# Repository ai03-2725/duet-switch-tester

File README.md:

# Duet Switch Tester

A switch tester intended for use at events and storefronts.  
Displays two of each switch - one with a keycap for testing the keyfeel, and another without a keycap to show off the visuals.  
Can be assembled with a functioning PCB to pair the tester to a kiosk device for additional information display purposes.  

## Features
- FR4 sandwich case
- Designed to look visually balanced with the left column of each cluster having keycaps installed
- Fully hotswap PCB powered by a RP2040
- Roughly 1800-size to balance display quantity with practicality and shipping/transport constraints

## BOM
Necessary for all builds:
- 1x Plate
- 1x Bottom panel
- 8x M2x8 Spacers
- 16x M2x5 wafer-head screws
- 10x 8mm diameter rubber feet
  
Necessary if planning to pair the device to a webapp or similar:
- 1x PCB (Optional if you're not looking to pair the tester to a device)
- Optional hotswap standoffs for anchoring the PCB to the plate
    - 10x M2x3.5 Spacers
    - 20x M2x3 wafer-head screws

## Restrictions
As per the [license](https://github.com/ai03-2725/duet-switch-tester/blob/main/LICENSE), any modified version must be fully disclosed and open-sourced under the same license.  
  
There is no warranty, liability, or support for this project.  
If you intend to use this project, do so at your own risk and under your own responsibility.

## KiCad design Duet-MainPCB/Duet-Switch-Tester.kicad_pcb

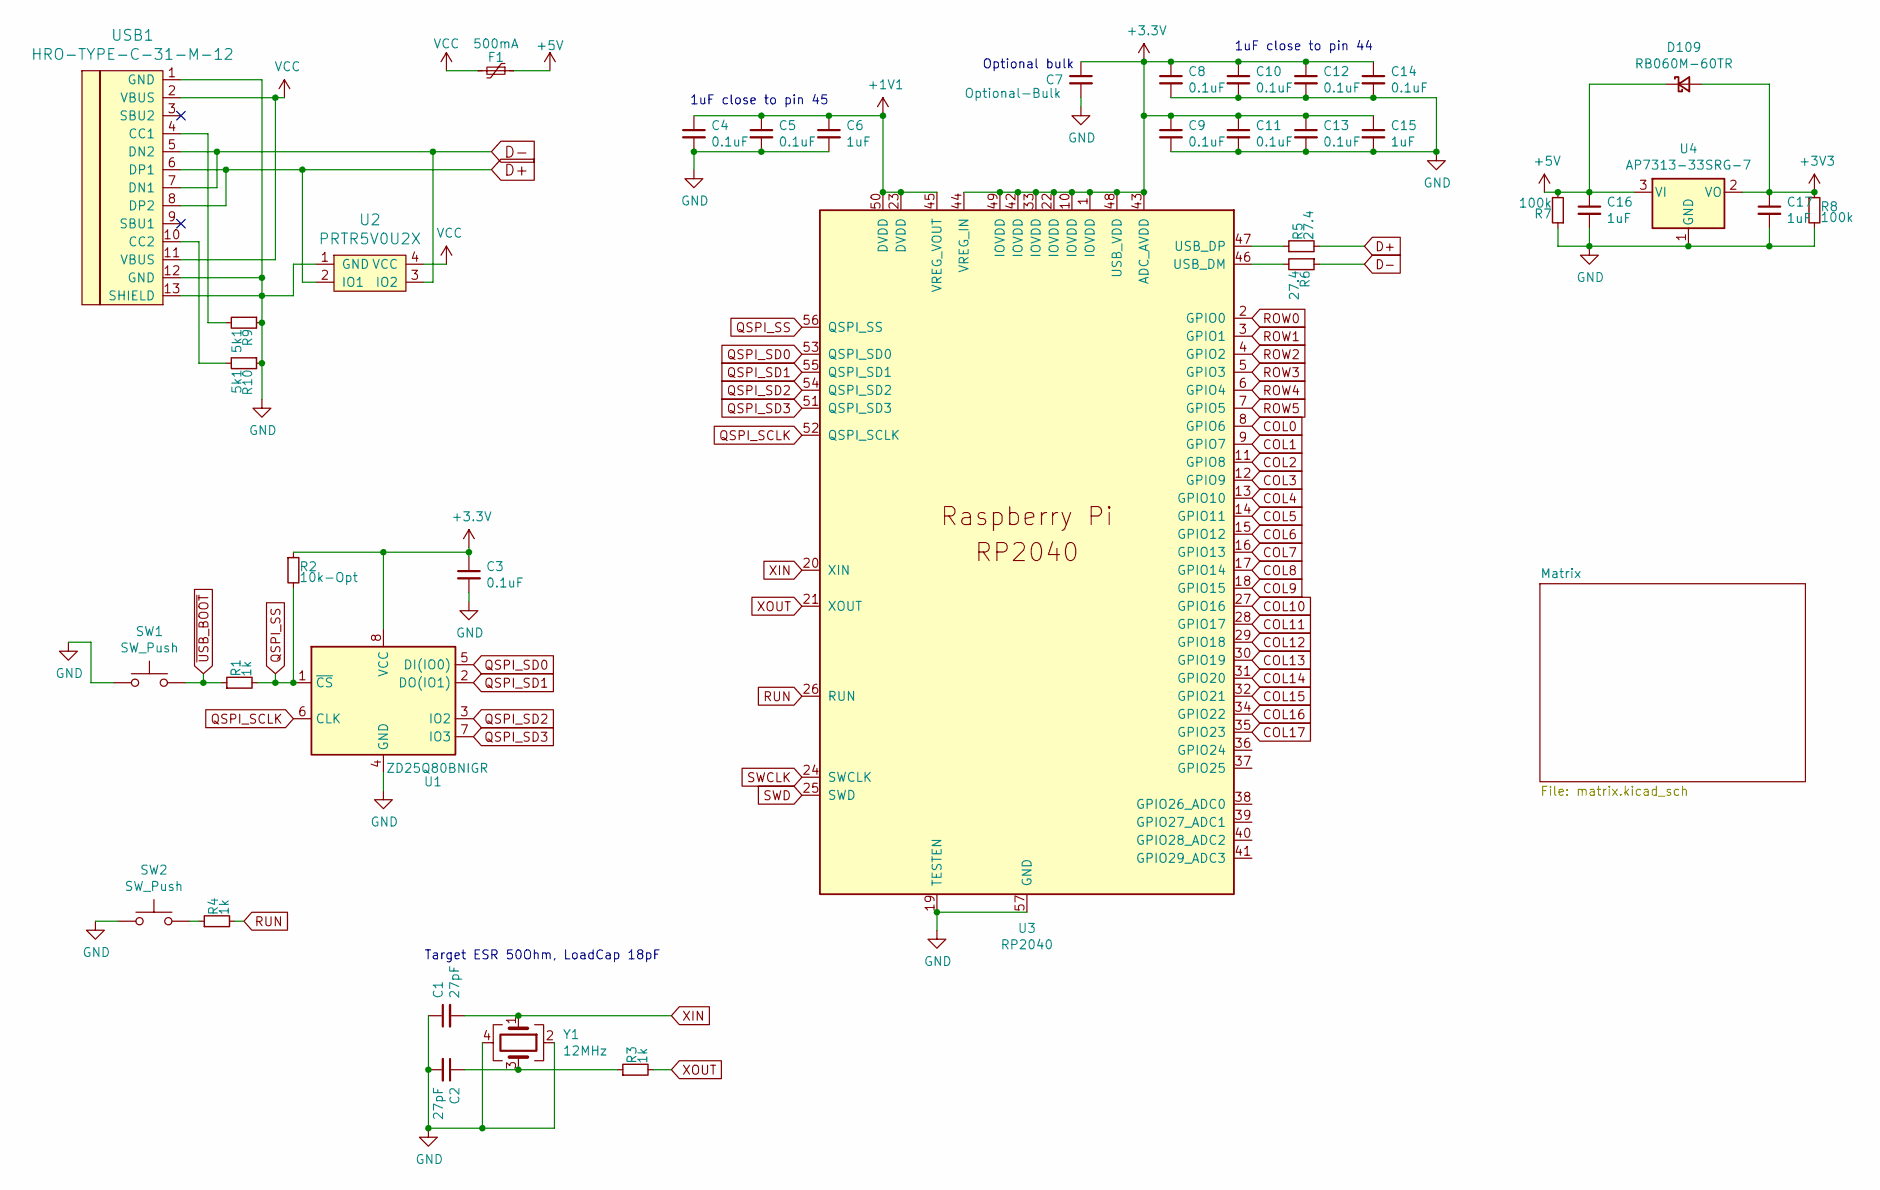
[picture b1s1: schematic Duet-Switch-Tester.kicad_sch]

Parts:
C1, C2: 27pF; C_0402_1005Metric
C3, C4, C5, C8, C9, C10, C11, C12, C13, C14: 0.1uF; C_0402_1005Metric
C6, C15, C16, C17: 1uF; C_0402_1005Metric
C7: Optional-Bulk; C_0603_1608Metric
D109: RB060M-60TR; D_SOD-123
F1: 500mA; Fuse_1206_3216Metric
R1, R3, R4: 1k; R_0402_1005Metric
R2: 10k-Opt; R_0402_1005Metric
R5, R6: 27.4; R_0402_1005Metric
R7, R8: 100k; R_0603_1608Metric
R9, R10: 5k1; R_0603_1608Metric
SW1, SW2: SW_Push; SW_SPST_TL3342
U1: ZD25Q80BNIGR; USON-8-1.5mm
U2: PRTR5V0U2X; SOT143B
U3: RP2040; RP2040-QFN-56
U4: AP7313-33SRG-7; SOT-23
USB1: HRO-TYPE-C-31-M-12; HRO-TYPE-C-31-M-12-Assembly
Y1: 12MHz; Crystal_SMD_3225-4Pin_3.2x2.5mm

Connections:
+1V1: C4.1, C5.1, C6.1, U3.23 (DVDD), U3.45 (VREG_VOUT), U3.50 (DVDD)
+5V: C16.1, D109.1 (K), F1.1, R7.2, U4.3 (VI)
COL0: U3.8 (GPIO6); also elsewhere on the board
COL1: U3.9 (GPIO7); also elsewhere on the board
COL2: U3.11 (GPIO8); also elsewhere on the board
COL3: U3.12 (GPIO9); also elsewhere on the board
COL4: U3.13 (GPIO10); also elsewhere on the board
COL5: U3.14 (GPIO11); also elsewhere on the board
COL6: U3.15 (GPIO12); also elsewhere on the board
COL7: U3.16 (GPIO13); also elsewhere on the board
COL8: U3.17 (GPIO14); also elsewhere on the board
COL9: U3.18 (GPIO15); also elsewhere on the board
COL10: U3.27 (GPIO16); also elsewhere on the board
COL11: U3.28 (GPIO17); also elsewhere on the board
COL12: U3.29 (GPIO18); also elsewhere on the board
COL13: U3.30 (GPIO19); also elsewhere on the board
COL14: U3.31 (GPIO20); also elsewhere on the board
COL15: U3.32 (GPIO21); also elsewhere on the board
COL16: U3.34 (GPIO22); also elsewhere on the board
COL17: U3.35 (GPIO23); also elsewhere on the board
D+: R5.2, U2.2 (IO1), USB1.6 (DP1), USB1.8 (DP2)
D-: R6.1, U2.3 (IO2), USB1.5 (DN2), USB1.7 (DN1)
GND: C1.1, C2.2, C3.2, C4.2, C5.2, C6.2, C7.2, C8.2, C9.2, C10.2, C11.2, C12.2, C13.2, C14.2, C15.2, C16.2, C17.2, R7.1, R8.2, R9.1, R10.1, SW1.1, SW2.1, U1.4 (GND), U2.1 (GND), U3.19 (TESTEN), U3.57 (GND), U4.1 (GND), USB1.1 (GND), USB1.12 (GND), USB1.13 (SHIELD), Y1.2, Y1.4
unnamed: C2.1, R3.1, Y1.3
unnamed: R4.1, SW2.2
unnamed: R6.2, U3.46 (USB_DM)
unnamed: R5.1, U3.47 (USB_DP)
unnamed: R9.2, USB1.4 (CC1)
unnamed: R10.2, USB1.10 (CC2)
QSPI_SCLK: U1.6 (CLK), U3.52 (QSPI_SCLK)
QSPI_SD0: U1.5 (DI(IO0)), U3.53 (QSPI_SD0)
QSPI_SD1: U1.2 (DO(IO1)), U3.55 (QSPI_SD1)
QSPI_SD2: U1.3 (IO2), U3.54 (QSPI_SD2)
QSPI_SD3: U1.7 (IO3), U3.51 (QSPI_SD3)
QSPI_SS: R1.2, R2.2, U1.1 (~CS), U3.56 (QSPI_SS)
ROW0: U3.2 (GPIO0); also elsewhere on the board
ROW1: U3.3 (GPIO1); also elsewhere on the board
ROW2: U3.4 (GPIO2); also elsewhere on the board
ROW3: U3.5 (GPIO3); also elsewhere on the board
ROW4: U3.6 (GPIO4); also elsewhere on the board
ROW5: U3.7 (GPIO5); also elsewhere on the board
RUN: R4.2, U3.26 (RUN)
SWCLK: U3.24 (SWCLK)
SWD: U3.25 (SWD)
VCC: F1.2, U2.4 (VCC), USB1.2 (VBUS), USB1.11 (VBUS)
XIN: C1.2, U3.20 (XIN), Y1.1
XOUT: R3.2, U3.21 (XOUT)
~USB_BOOT: R1.1, SW1.2

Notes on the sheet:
Target ESR 50Ohm, LoadCap 18pF
Optional bulk
1uF close to pin 44
1uF close to pin 45

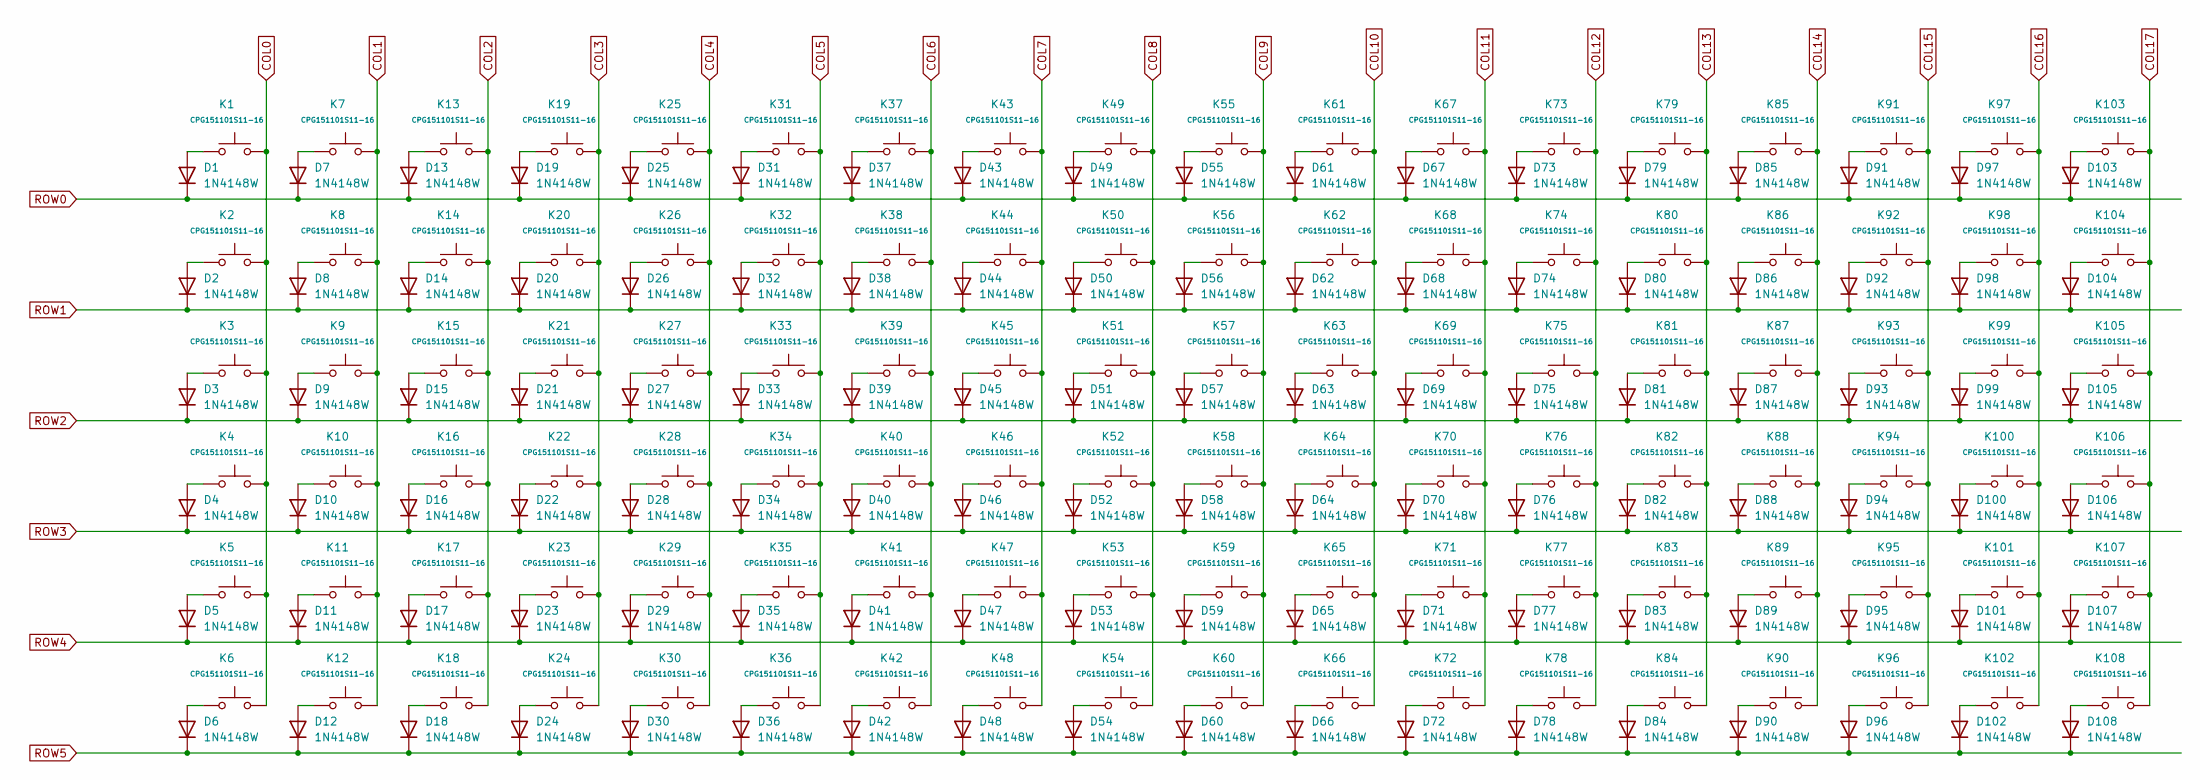
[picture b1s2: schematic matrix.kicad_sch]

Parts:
D1, D2, D3, D4, D5, D6, D7, D8, D9, D10, D11, D12, D13, D14, D15, D16, D17, D18, D19, D20, D21, D22, D23, D24, D25, D26, D27, D28, D29, D30, D31, D32, D33, D34, D35, D36, D37, D38, D39, D40, D41, D42, D43, D44, D45, D46, D47, D48, D49, D50, D51, D52, D53, D54, D55, D56, D57, D58, D59, D60, D61, D62, D63, D64, D65, D66, D67, D68, D69, D70, D71, D72, D73, D74, D75, D76, D77, D78, D79, D80, D81, D82, D83, D84, D85, D86, D87, D88, D89, D90, D91, D92, D93, D94, D95, D96, D97, D98, D99, D100, D101, D102, D103, D104, D105, D106, D107, D108: 1N4148W; D_SOD-123
K1, K2, K3, K4, K5, K6, K7, K8, K9, K10, K11, K12, K13, K14, K15, K16, K17, K18, K19, K20, K21, K22, K23, K24, K25, K26, K27, K28, K29, K30, K31, K32, K33, K34, K35, K36, K37, K38, K39, K40, K41, K42, K43, K44, K45, K46, K47, K48, K49, K50, K51, K52, K53, K54, K55, K56, K57, K58, K59, K60, K61, K62, K63, K64, K65, K66, K67, K68, K69, K70, K71, K72, K73, K74, K75, K76, K77, K78, K79, K80, K81, K82, K83, K84, K85, K86, K87, K88, K89, K90, K91, K92, K93, K94, K95, K96, K97, K98, K99, K100, K101, K102, K103, K104, K105, K106, K107, K108: CPG151101S11-16; MX-Hotswap-1U

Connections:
COL0: K1.2, K2.2, K3.2, K4.2, K5.2, K6.2; also elsewhere on the board
COL1: K7.2, K8.2, K9.2, K10.2, K11.2, K12.2; also elsewhere on the board
COL2: K13.2, K14.2, K15.2, K16.2, K17.2, K18.2; also elsewhere on the board
COL3: K19.2, K20.2, K21.2, K22.2, K23.2, K24.2; also elsewhere on the board
COL4: K25.2, K26.2, K27.2, K28.2, K29.2, K30.2; also elsewhere on the board
COL5: K31.2, K32.2, K33.2, K34.2, K35.2, K36.2; also elsewhere on the board
COL6: K37.2, K38.2, K39.2, K40.2, K41.2, K42.2; also elsewhere on the board
COL7: K43.2, K44.2, K45.2, K46.2, K47.2, K48.2; also elsewhere on the board
COL8: K49.2, K50.2, K51.2, K52.2, K53.2, K54.2; also elsewhere on the board
COL9: K55.2, K56.2, K57.2, K58.2, K59.2, K60.2; also elsewhere on the board
COL10: K61.2, K62.2, K63.2, K64.2, K65.2, K66.2; also elsewhere on the board
COL11: K67.2, K68.2, K69.2, K70.2, K71.2, K72.2; also elsewhere on the board
COL12: K73.2, K74.2, K75.2, K76.2, K77.2, K78.2; also elsewhere on the board
COL13: K79.2, K80.2, K81.2, K82.2, K83.2, K84.2; also elsewhere on the board
COL14: K85.2, K86.2, K87.2, K88.2, K89.2, K90.2; also elsewhere on the board
COL15: K91.2, K92.2, K93.2, K94.2, K95.2, K96.2; also elsewhere on the board
COL16: K97.2, K98.2, K99.2, K100.2, K101.2, K102.2; also elsewhere on the board
COL17: K103.2, K104.2, K105.2, K106.2, K107.2, K108.2; also elsewhere on the board
unnamed: D1.2 (A), K1.1
unnamed: D2.2 (A), K2.1
unnamed: D3.2 (A), K3.1
unnamed: D4.2 (A), K4.1
unnamed: D5.2 (A), K5.1
unnamed: D6.2 (A), K6.1
unnamed: D7.2 (A), K7.1
unnamed: D8.2 (A), K8.1
unnamed: D9.2 (A), K9.1
unnamed: D10.2 (A), K10.1
unnamed: D11.2 (A), K11.1
unnamed: D12.2 (A), K12.1
unnamed: D13.2 (A), K13.1
unnamed: D14.2 (A), K14.1
unnamed: D15.2 (A), K15.1
unnamed: D16.2 (A), K16.1
unnamed: D17.2 (A), K17.1
unnamed: D18.2 (A), K18.1
unnamed: D19.2 (A), K19.1
unnamed: D20.2 (A), K20.1
unnamed: D21.2 (A), K21.1
unnamed: D22.2 (A), K22.1
unnamed: D23.2 (A), K23.1
unnamed: D24.2 (A), K24.1
unnamed: D25.2 (A), K25.1
unnamed: D26.2 (A), K26.1
unnamed: D27.2 (A), K27.1
unnamed: D28.2 (A), K28.1
unnamed: D29.2 (A), K29.1
unnamed: D30.2 (A), K30.1
unnamed: D31.2 (A), K31.1
unnamed: D32.2 (A), K32.1
unnamed: D33.2 (A), K33.1
unnamed: D34.2 (A), K34.1
unnamed: D35.2 (A), K35.1
unnamed: D36.2 (A), K36.1
unnamed: D37.2 (A), K37.1
unnamed: D38.2 (A), K38.1
unnamed: D39.2 (A), K39.1
unnamed: D40.2 (A), K40.1
unnamed: D41.2 (A), K41.1
unnamed: D42.2 (A), K42.1
unnamed: D43.2 (A), K43.1
unnamed: D44.2 (A), K44.1
unnamed: D45.2 (A), K45.1
unnamed: D46.2 (A), K46.1
unnamed: D47.2 (A), K47.1
unnamed: D48.2 (A), K48.1
unnamed: D49.2 (A), K49.1
unnamed: D50.2 (A), K50.1
unnamed: D51.2 (A), K51.1
unnamed: D52.2 (A), K52.1
unnamed: D53.2 (A), K53.1
unnamed: D54.2 (A), K54.1
unnamed: D55.2 (A), K55.1
unnamed: D56.2 (A), K56.1
unnamed: D57.2 (A), K57.1
unnamed: D58.2 (A), K58.1
unnamed: D59.2 (A), K59.1
unnamed: D60.2 (A), K60.1
unnamed: D61.2 (A), K61.1
unnamed: D62.2 (A), K62.1
unnamed: D63.2 (A), K63.1
unnamed: D64.2 (A), K64.1
unnamed: D65.2 (A), K65.1
unnamed: D66.2 (A), K66.1
unnamed: D67.2 (A), K67.1
unnamed: D68.2 (A), K68.1
unnamed: D69.2 (A), K69.1
unnamed: D70.2 (A), K70.1
unnamed: D71.2 (A), K71.1
unnamed: D72.2 (A), K72.1
unnamed: D73.2 (A), K73.1
unnamed: D74.2 (A), K74.1
unnamed: D75.2 (A), K75.1
unnamed: D76.2 (A), K76.1
unnamed: D77.2 (A), K77.1
unnamed: D78.2 (A), K78.1
unnamed: D79.2 (A), K79.1
unnamed: D80.2 (A), K80.1
unnamed: D81.2 (A), K81.1
unnamed: D82.2 (A), K82.1
unnamed: D83.2 (A), K83.1
unnamed: D84.2 (A), K84.1
unnamed: D85.2 (A), K85.1
unnamed: D86.2 (A), K86.1
unnamed: D87.2 (A), K87.1
unnamed: D88.2 (A), K88.1
unnamed: D89.2 (A), K89.1
unnamed: D90.2 (A), K90.1
unnamed: D91.2 (A), K91.1
unnamed: D92.2 (A), K92.1
unnamed: D93.2 (A), K93.1
unnamed: D94.2 (A), K94.1
unnamed: D95.2 (A), K95.1
unnamed: D96.2 (A), K96.1
unnamed: D97.2 (A), K97.1
unnamed: D98.2 (A), K98.1
unnamed: D99.2 (A), K99.1
unnamed: D100.2 (A), K100.1
unnamed: D101.2 (A), K101.1
unnamed: D102.2 (A), K102.1
unnamed: D103.2 (A), K103.1
unnamed: D104.2 (A), K104.1
unnamed: D105.2 (A), K105.1
unnamed: D106.2 (A), K106.1
unnamed: D107.2 (A), K107.1
unnamed: D108.2 (A), K108.1
ROW0: D1.1 (K), D7.1 (K), D13.1 (K), D19.1 (K), D25.1 (K), D31.1 (K), D37.1 (K), D43.1 (K), D49.1 (K), D55.1 (K), D61.1 (K), D67.1 (K), D73.1 (K), D79.1 (K), D85.1 (K), D91.1 (K), D97.1 (K), D103.1 (K); also elsewhere on the board
ROW1: D2.1 (K), D8.1 (K), D14.1 (K), D20.1 (K), D26.1 (K), D32.1 (K), D38.1 (K), D44.1 (K), D50.1 (K), D56.1 (K), D62.1 (K), D68.1 (K), D74.1 (K), D80.1 (K), D86.1 (K), D92.1 (K), D98.1 (K), D104.1 (K); also elsewhere on the board
ROW2: D3.1 (K), D9.1 (K), D15.1 (K), D21.1 (K), D27.1 (K), D33.1 (K), D39.1 (K), D45.1 (K), D51.1 (K), D57.1 (K), D63.1 (K), D69.1 (K), D75.1 (K), D81.1 (K), D87.1 (K), D93.1 (K), D99.1 (K), D105.1 (K); also elsewhere on the board
ROW3: D4.1 (K), D10.1 (K), D16.1 (K), D22.1 (K), D28.1 (K), D34.1 (K), D40.1 (K), D46.1 (K), D52.1 (K), D58.1 (K), D64.1 (K), D70.1 (K), D76.1 (K), D82.1 (K), D88.1 (K), D94.1 (K), D100.1 (K), D106.1 (K); also elsewhere on the board
ROW4: D5.1 (K), D11.1 (K), D17.1 (K), D23.1 (K), D29.1 (K), D35.1 (K), D41.1 (K), D47.1 (K), D53.1 (K), D59.1 (K), D65.1 (K), D71.1 (K), D77.1 (K), D83.1 (K), D89.1 (K), D95.1 (K), D101.1 (K), D107.1 (K); also elsewhere on the board
ROW5: D6.1 (K), D12.1 (K), D18.1 (K), D24.1 (K), D30.1 (K), D36.1 (K), D42.1 (K), D48.1 (K), D54.1 (K), D60.1 (K), D66.1 (K), D72.1 (K), D78.1 (K), D84.1 (K), D90.1 (K), D96.1 (K), D102.1 (K), D108.1 (K); also elsewhere on the board

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
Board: 2 copper layers, 253 parts (145 on the bottom side), 155 nets, no tracks yet.

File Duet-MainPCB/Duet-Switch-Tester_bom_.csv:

Component,Description,Part,References,Value,Footprint,Quantity Per PCB,Datasheet,Sim.Device,Sim.Pins
1,"Unpolarized capacitor, small symbol",C_Small,C1 C2,27pF,C_0402_1005Metric,2,~,,
2,"Unpolarized capacitor, small symbol",C_Small,C3 C4 C5 C8 C9 C10 C11 C12 C13 C14,0.1uF,C_0402_1005Metric,10,~,,
3,"Unpolarized capacitor, small symbol",C_Small,C6 C15 C16 C17,1uF,C_0402_1005Metric,4,~,,
4,"Unpolarized capacitor, small symbol",C_Small,C7,10uF-OPT,C_0603_1608Metric,1,~,,
5,"75V 0.15A Fast Switching Diode, SOD-123",1N4148W,D1 D2 D3 D4 D5 D6 D7 D8 D9 D10 D11 D12 D13 D14 D15 D16 D17 D18 D19 D20 D21 D22 D23 D24 D25 D26 D27 D28 D29 D30 D31 D32 D33 D34 D35 D36 D37 D38 D39 D40 D41 D42 D43 D44 D45 D46 D47 D48 D49 D50 D51 D52 D53 D54 D55 D56 D57 D58 D59 D60 D61 D62 D63 D64 D65 D66 D67 D68 D69 D70 D71 D72 D73 D74 D75 D76 D77 D78 D79 D80 D81 D82 D83 D84 D85 D86 D87 D88 D89 D90 D91 D92 D93 D94 D95 D96 D97 D98 D99 D100 D101 D102 D103 D104 D105 D106 D107 D108,1N4148W,D_SOD-123-MinimalPrint,108,https://www.vishay.com/docs/85748/1n4148w.pdf,D,1=K 2=A
6,"Schottky diode, small symbol",D_Schottky_Small,D109,RB060M-60TR,D_SOD-123,1,~,,
7,"Resettable fuse, polymeric positive temperature coefficient, small symbol",Polyfuse_Small,F1,500mA,Fuse_1206_3216Metric,1,~,,
8,"Push button switch, generic, two pins",SW_Push,K1 K2 K3 K4 K5 K6 K7 K8 K9 K10 K11 K12 K13 K14 K15 K16 K17 K18 K19 K20 K21 K22 K23 K24 K25 K26 K27 K28 K29 K30 K31 K32 K33 K34 K35 K36 K37 K38 K39 K40 K41 K42 K43 K44 K45 K46 K47 K48 K49 K50 K51 K52 K53 K54 K55 K56 K57 K58 K59 K60 K61 K62 K63 K64 K65 K66 K67 K68 K69 K70 K71 K72 K73 K74 K75 K76 K77 K78 K79 K80 K81 K82 K83 K84 K85 K86 K87 K88 K89 K90 K91 K92 K93 K94 K95 K96 K97 K98 K99 K100 K101 K102 K103 K104 K105 K106 K107 K108,CPG151101S11-16,MX-Hotswap-1U,108,~,,
9,"Resistor, small symbol",R_Small,R5 R6,27.4,R_0402_1005Metric,2,~,,
10,"Resistor, small symbol",R_Small,R1 R3 R4,1k,R_0402_1005Metric,3,~,,
11,"Resistor, small symbol",R_Small,R9 R10,5k1,R_0603_1608Metric,2,~,,
12,"Resistor, small symbol",R_Small,R7 R8,100k,R_0603_1608Metric,2,~,,
13,"Resistor, small symbol",R_Small,R2,10k-OPT,R_0402_1005Metric,1,~,,
14,"Push button switch, generic, two pins",SW_Push,SW1 SW2,SW_Push,SW_SPST_TL3342,2,~,,
15,"250mA Low Quiscent Current LDO, 3.0V output, SOT-23",MCP1700-3002E_SOT23,U4,AP7313-33SRG-7,SOT-23,1,http://ww1.microchip.com/downloads/en/DeviceDoc/20001826D.pdf,,
16,,PRTR5V0U2X,U2,PRTR5V0U2X,SOT143B,1,,,
17,,RP2040,U3,RP2040,RP2040-QFN-56,1,,,
18,"32Mb Serial Flash Memory, Standard/Dual/Quad SPI, SOIC-8",W25Q32JVSS,U1,ZD25Q80BNIGR,USON-8-1.5mm,1,http://www.winbond.com/resource-files/w25q32jv%20revg%200327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,,
19,,HRO-TYPE-C-31-M-12,USB1,HRO-TYPE-C-31-M-12,HRO-TYPE-C-31-M-12-Assembly,1,,,
20,"Four pin crystal, GND on pins 2 and 4",Crystal_GND24,Y1,12MHz,Crystal_SMD_3225-4Pin_3.2x2.5mm,1,~,,





Component Groups:,20
Component Count:,253
Fitted Components:,253
Number of PCBs:,1
Total components:,253
Schematic Version:,
Schematic Date:,
PCB Variant:,default
BoM Date:,9/25/2023 11:44:36 AM
Schematic Source:,Duet-Switch-Tester.kicad_sch
KiCad Version:,Eeschema 7.0.7

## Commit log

2023-09-16 Begin project
2023-09-24 Route PCB
2023-09-25 Finish PCB; add case DXF files
2023-09-25 Make FR4 plate data
2023-09-25 Make FR4 bottom data
2023-09-25 Make case parts prettier
2023-09-25 Generate production data
2023-09-25 Make initial JLC files
2023-09-25 Improve JLC files
2023-09-25 Correct socket orientation
2023-10-29 Add cover image
2023-10-29 Add image to readme
2023-10-29 Add section regarding license
